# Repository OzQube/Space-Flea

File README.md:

# Space-Flea
Design documents for the Space Flea project on Hackaday.io

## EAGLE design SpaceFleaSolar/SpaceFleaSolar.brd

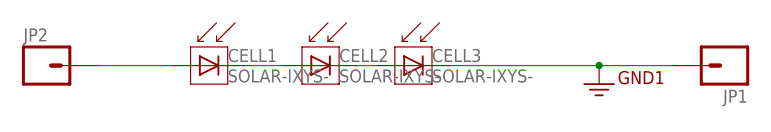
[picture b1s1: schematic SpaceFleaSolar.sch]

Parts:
CELL1, CELL2, CELL3: SOLAR-IXYS-; SOLARBIT-12X1
JP1, JP2: M01PTH_2MM; 1X01_2MM

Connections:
GND: CELL3.- (C), JP1.1
unnamed: CELL1.- (C), CELL2.+ (A)
unnamed: CELL2.- (C), CELL3.+ (A)
PLUS: CELL1.+ (A), JP2.1

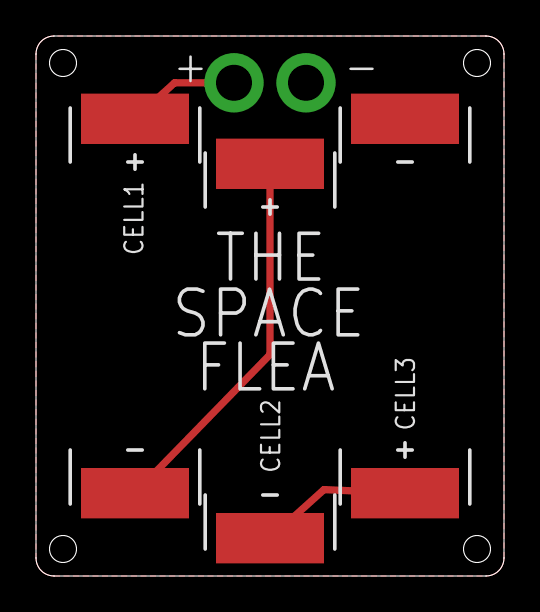
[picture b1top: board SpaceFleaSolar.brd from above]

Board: 2 copper layers, 26.0 x 30.0 mm, 5 parts (0 on the bottom side), 4 nets.

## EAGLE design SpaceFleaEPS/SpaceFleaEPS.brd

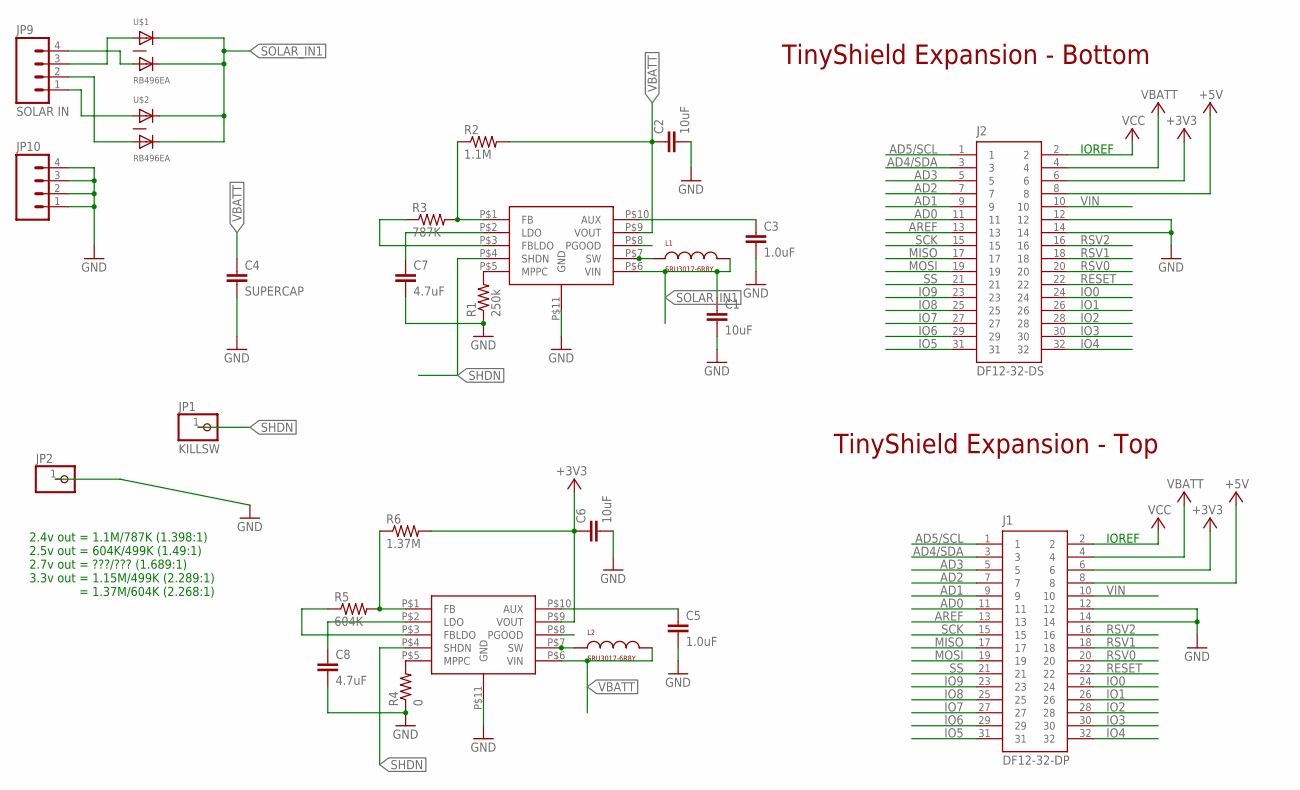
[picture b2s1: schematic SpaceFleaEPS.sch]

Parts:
C1, C2, C6: 10uF; 0805
C3, C5: 1.0uF; 0603-CAP
C4: SUPERCAP; CAP-PTH-5MM
C7, C8: 4.7uF; 0603-CAP
J1: DF12-32-DP; PARTNO AS-ITM-00015
J2: DF12-32-DS; PARTNO AS-ITM-00012
JP1: KILLSW; 1X01_2MM
JP2: HEADER-1X12MM; 1X01_2MM
JP9: SOLAR IN; 1X04-1.27MM
JP10: M041.27MM; 1X04-1.27MM
L1, L2: SRU3017-6R8Y
R1: 250k; 0402-RES
R2: 1.1M; 0402-RES
R3: 787K; 0402-RES
R4: 0; 0402-RES
R5: 604K; 0402-RES
R6: 1.37M; 0402-RES
U$1, U$2: RB496EA; SOT23-5
U$3, U$5: LTC3105_DFN; LTC3105DFN

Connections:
+3V3: C6.1, J1.6, J2.6, R6.2, U$3.P$9 (VOUT)
+5V: J1.8, J2.8
AD0: J1.11, J2.11
AD1: J1.9, J2.9
AD2: J1.7, J2.7
AD3: J1.5, J2.5
AD4/SDA: J1.3, J2.3
AD5/SCL: J1.1, J2.1
AREF: J1.13, J2.13
GND: C1.2, C2.2, C3.2, C4.2, C5.2, C6.2, C7.2, C8.2, J1.12, J1.14, J2.12, J2.14, JP2.1, JP10.1, JP10.2, JP10.3, JP10.4, R1.1, R3.1, R4.1, R5.1, U$3.P$3 (FBLDO), U$3.P$11 (GND), U$5.P$3 (FBLDO), U$5.P$11 (GND)
IO0: J1.24, J2.24
IO1: J1.26, J2.26
IO2: J1.28, J2.28
IO3: J1.30, J2.30
IO4: J1.32, J2.32
IO5: J1.31, J2.31
IO6: J1.29, J2.29
IO7: J1.27, J2.27
IO8: J1.25, J2.25
IO9: J1.23, J2.23
MISO: J1.17, J2.17
MOSI: J1.19, J2.19
unnamed: JP9.3, U$1.1
unnamed: JP9.4, U$1.3
unnamed: JP9.2, U$2.3
unnamed: JP9.1, U$2.1
unnamed: C3.1, U$5.P$10 (AUX)
unnamed: C7.1, U$5.P$2 (LDO)
unnamed: R4.2, U$3.P$5 (MPPC)
unnamed: R5.2, R6.1, U$3.P$1 (FB)
unnamed: L2.P$1, U$3.P$7 (SW)
unnamed: R1.2, U$5.P$5 (MPPC)
unnamed: C5.1, U$3.P$10 (AUX)
unnamed: C8.1, U$3.P$2 (LDO)
unnamed: R2.1, R3.2, U$5.P$1 (FB)
unnamed: L1.P$1, U$5.P$7 (SW)
RESET: J1.22, J2.22
RSV0: J1.20, J2.20
RSV1: J1.18, J2.18
RSV2: J1.16, J2.16
SCK: J1.15, J2.15
SHDN: JP1.1, U$3.P$4 (SHDN), U$5.P$4 (SHDN)
SOLAR_IN1: C1.1, L1.P$2, U$1.4, U$1.5, U$2.4, U$2.5, U$5.P$6 (VIN)
SS: J1.21, J2.21
VBATT: C2.1, C4.1, J1.4, J2.4, L2.P$2, R2.2, U$3.P$6 (VIN), U$5.P$9 (VOUT)
VCC: J1.2, J2.2
VIN: J1.10, J2.10

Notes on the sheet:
TinyShield Expansion - Bottom
IOREF
TinyShield Expansion - Top
2.4v out = 1.1M/787K (1.398:1) 2.5v out = 604K/499K (1.49:1) 2.7v out = ???/??? (1.689:1) 3.3v out = 1.15M/499K (2.289:1) = 1.37M/604K (2.268:1)

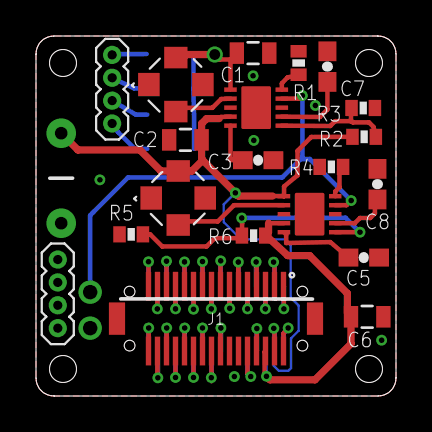
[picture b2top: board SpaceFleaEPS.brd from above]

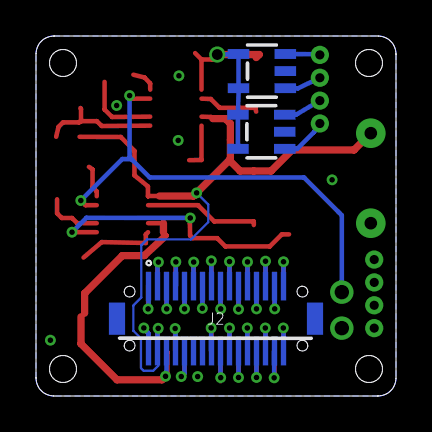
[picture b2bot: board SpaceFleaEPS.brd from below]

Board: 2 copper layers, 20.0 x 20.0 mm, 26 parts (3 on the bottom side), 47 nets.

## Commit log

2016-04-29 File upload
2016-06-02 Added STL

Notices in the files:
parts and their libraries:
SparkFun-Connectors: Licensing: Creative Commons ShareAlike 4.0 International - https://creativecommons.org/licenses/by-sa/4.0
microbuilder: This work is placed in the public domain, and may be freely used for commercial and non-commercial work with the following conditions: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
